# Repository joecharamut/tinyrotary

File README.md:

# tinyrotary

making a rotary encoder i2c peripheral thingy

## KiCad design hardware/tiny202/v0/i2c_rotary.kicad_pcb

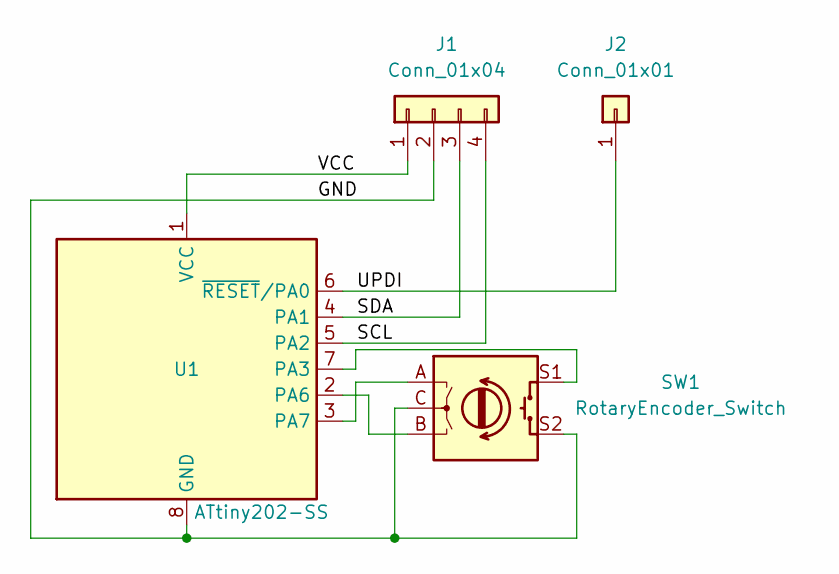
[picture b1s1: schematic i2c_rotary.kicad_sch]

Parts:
J1: Conn_01x04; PinHeader_1x04_P2.54mm_Vertical
J2: Conn_01x01; PinHeader_1x01_P2.54mm_Vertical
SW1: RotaryEncoder_Switch; RotaryEncoder_Alps_EC11E-Switch_Vertical_H20mm
U1: ATtiny202-SS; SOIC-8_3.9x4.9mm_P1.27mm

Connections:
/GND: J1.2, SW1.C, SW1.S2, U1.8 (GND)
/SCL: J1.4, U1.5 (PA2)
/SDA: J1.3, U1.4 (PA1)
/UPDI: J2.1, U1.6 (~RESET/PA0)
/VCC: J1.1, U1.1 (VCC)
unnamed: SW1.S1, U1.7 (PA3)
unnamed: SW1.B, U1.2 (PA6)
unnamed: SW1.A, U1.3 (PA7)

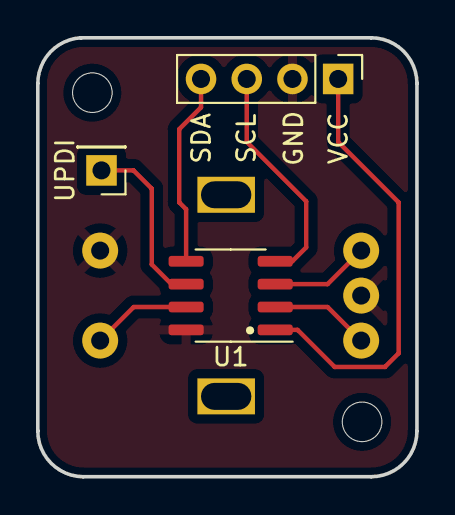
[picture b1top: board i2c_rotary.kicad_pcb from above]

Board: 2 copper layers, 21.1 x 24.4 mm, 6 parts (1 on the bottom side), 8 nets.

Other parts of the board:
M1, M2: MountingHole_2.2mm_M2

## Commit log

2023-01-15 basically works
2023-01-17 kinda works?
2023-01-17 rev2
2023-01-28 setup for attiny202
2023-01-28 move old hardware
2023-01-28 add new hardware
2023-01-30 slowly working on porting
2023-02-02 split config into its own file
2023-02-02 more cooode
2023-02-04 working on twi
2023-03-11 codin
